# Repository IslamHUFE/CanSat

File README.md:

## CanSat

This is the repository for the project of its ambitious owner.

I hope the effort put into this will not be wasted.

### Electrical and microcontroller system

#### CanSat

#### Base station

### Mechnical

#### CanSat

#### Base station

### Documentation

### Owner

### LICENSE

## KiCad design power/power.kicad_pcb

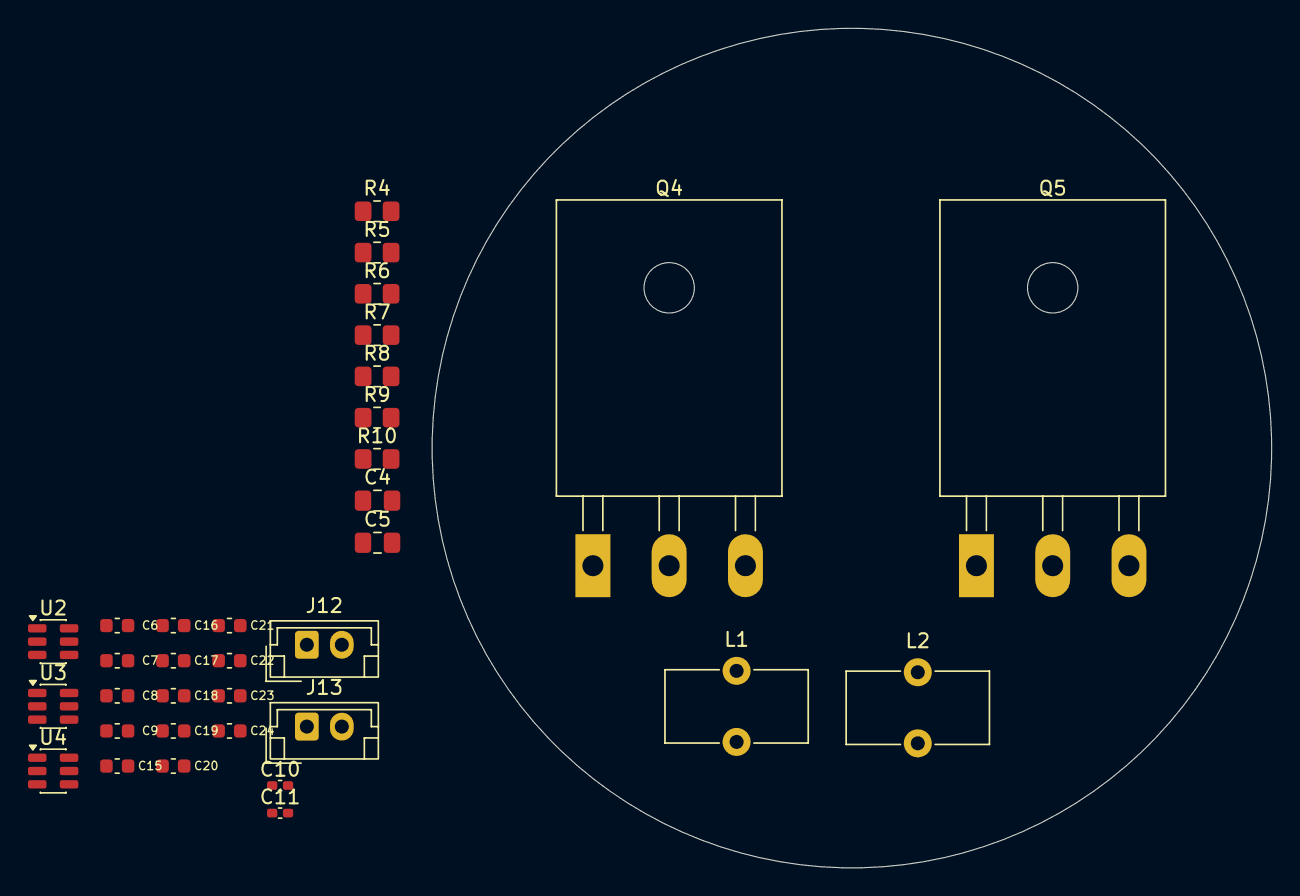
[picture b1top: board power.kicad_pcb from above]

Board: 2 copper layers, 60.0 x 60.0 mm, 34 parts (0 on the bottom side), 15 nets, no tracks yet.

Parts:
C4, C5: C_Polarized; C_0805_2012Metric_Pad1.18x1.45mm_HandSolder
C6, C7, C8, C9, C15, C16, C17, C18, C20, C21, C22, C23: 22uf/10V; C_0603_1608Metric
C10, C11: 100nf/50V; C_0402_1005Metric_Pad0.74x0.62mm_HandSolder
C19, C24: 100uf/10V; C_0603_1608Metric
J12, J13: Screw_Terminal_01x02; JST_EH_B2B-EH-A_1x02_P2.50mm_Vertical
L1, L2: 2.2uH/4.3A; L_Toroid_Vertical_L10.0mm_W5.0mm_P5.08mm
Q4, Q5: Q_NMOS; TO-247-3_Horizontal_TabDown
R4, R5, R6, R7, R8, R9, R10: R_US; R_0805_2012Metric_Pad1.20x1.40mm_HandSolder
U2: SOT-23-6
U3, U4: LM2734X; TSOT-23-6

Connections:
+3.3V: C15.2, C16.2, C17.2, C18.2, C19.2, L2.2, R9.2
+5V: C20.2, C21.2, C22.2, C23.2, C24.2, L1.2, R7.2
unnamed: C4.2, C5.2, J12.1, U2.6 (VSS)
unnamed: C5.1, J12.2, J13.1, R5.2
unnamed: R6.2, U2.3 (CS)
unnamed: R5.1, U2.4 (VC)
unnamed: R4.1, U2.5 (VDD)
unnamed: C10.1, U3.1 (BOOST)
unnamed: R7.1, R8.2, U3.3 (FB)
unnamed: C10.2, L1.1, U3.6 (SW)
unnamed: C11.1, U4.1 (BOOST)
unnamed: R9.1, R10.2, U4.3 (FB)
unnamed: C11.2, L2.1, U4.6 (SW)
PB+: C4.1, C6.1, C7.2, C8.1, C9.2, J13.2, R4.2, U3.4 (EN), U3.5 (VIN), U4.4 (EN), U4.5 (VIN)
PB-: C6.2, C7.1, C8.2, C9.1, C15.1, C16.1, C17.1, C18.1, C19.1, C20.1, C21.1, C22.1, C23.1, C24.1, R6.1, R8.1, R10.1, U3.2 (GND), U4.2 (GND)

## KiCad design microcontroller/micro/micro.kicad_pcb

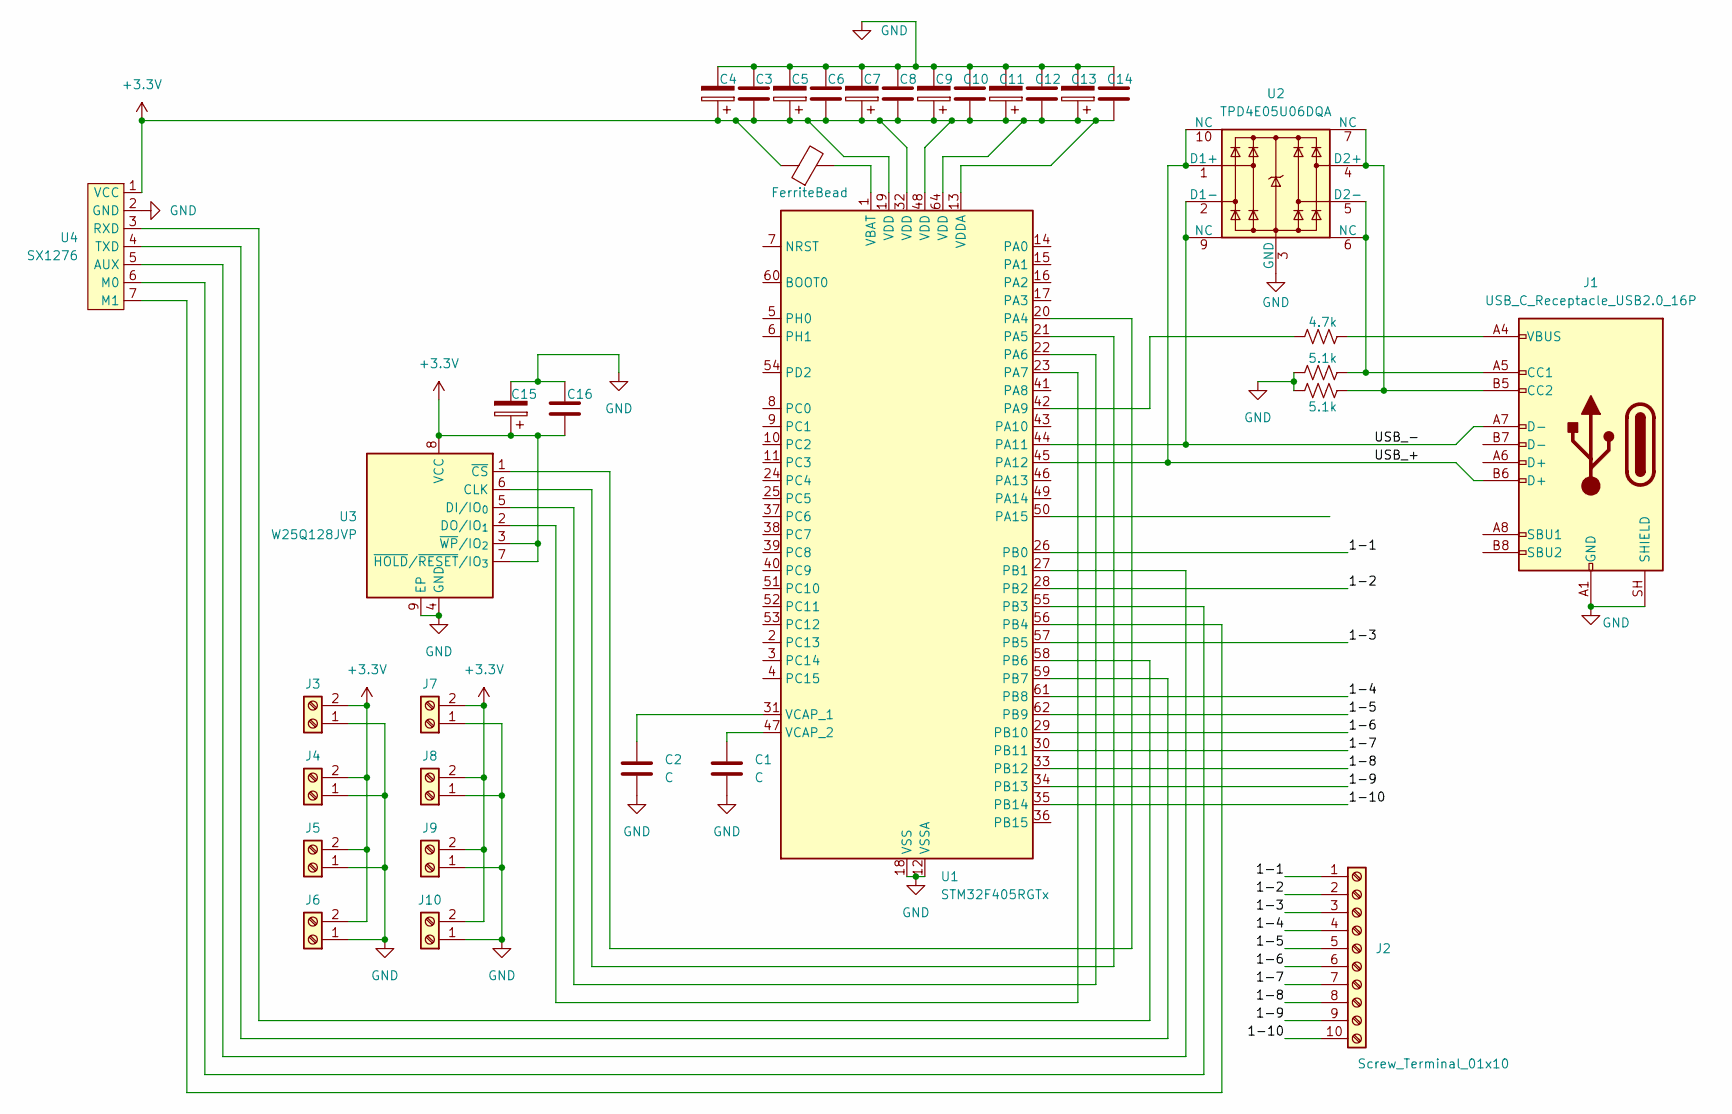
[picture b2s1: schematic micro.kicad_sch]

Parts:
C1, C2, C3, C6, C8, C10, C12, C14, C16: C; C_1206_3216Metric
C4, C5, C7, C9, C11, C13, C15: C_Polarized; CP_EIA-6032-28_Kemet-C
FB1: FerriteBead; L_Walsin_WLFM201609x
J1: USB_C_Receptacle_USB2.0_16P; USB_C_Receptacle_GCT_USB4105-xx-A_16P_TopMnt_Horizontal
J2: Screw_Terminal_01x10; PinHeader_1x10_P2.54mm_Vertical
J3, J4, J5, J6, J7, J8, J9, J10: Screw_Terminal_01x02; PinHeader_1x02_P2.54mm_Vertical
R1, R2: 5.1k; R_1206_3216Metric
R3: 4.7k; R_0603_1608Metric
U1: STM32F405RGTx; LQFP-64_10x10mm_P0.5mm
U2: TPD4E05U06DQA; USON-10_2.5x1.0mm_P0.5mm
U3: W25Q128JVP; WSON-8-1EP_6x5mm_P1.27mm_EP3.4x4.3mm
U4: SX1276; PinHeader_1x07_P2.54mm_Vertical

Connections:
+3.3V: C3.1, C4.1, C5.1, C6.1, C7.1, C8.1, C9.1, C10.1, C11.1, C12.1, C13.1, C14.1, C15.1, C16.1, FB1.1, J3.2, J4.2, J5.2, J6.2, J7.2, J8.2, J9.2, J10.2, U1.13 (VDDA), U1.19 (VDD), U1.32 (VDD), U1.48 (VDD), U1.64 (VDD), U3.3 (~WP/IO_{2}), U3.7 (~HOLD/~RESET/IO_{3}), U3.8 (VCC), U4.1 (VCC)
/1-1: J2.1, U1.26 (PB0)
/1-2: J2.2, U1.28 (PB2)
/1-3: J2.3, U1.57 (PB5)
/1-4: J2.4, U1.61 (PB8)
/1-5: J2.5, U1.62 (PB9)
/1-6: J2.6, U1.29 (PB10)
/1-7: J2.7, U1.30 (PB11)
/1-8: J2.8, U1.33 (PB12)
/1-9: J2.9, U1.34 (PB13)
/1-10: J2.10, U1.35 (PB14)
/USB_+: J1.B6 (D+), U1.45 (PA12), U2.1 (D1+), U2.10 (NC)
/USB_-: J1.A7 (D-), U1.44 (PA11), U2.2 (D1-), U2.9 (NC)
GND: C1.2, C2.2, C3.2, C4.2, C5.2, C6.2, C7.2, C8.2, C9.2, C10.2, C11.2, C12.2, C13.2, C14.2, C15.2, C16.2, J1.A1 (GND), J1.A12 (GND), J1.B1 (GND), J1.B12 (GND), J1.SH (SHIELD), J3.1, J4.1, J5.1, J6.1, J7.1, J8.1, J9.1, J10.1, R1.1, R2.1, U1.12 (VSSA), U1.18 (VSS), U1.63 (VSS), U2.3 (GND), U2.8 (GND), U3.4 (GND), U3.9 (EP), U4.2 (GND)
unnamed: J1.A5 (CC1), R2.2, U2.5 (D2-), U2.6 (NC)
unnamed: J1.B5 (CC2), R1.2, U2.4 (D2+), U2.7 (NC)
unnamed: J1.A4 (VBUS), J1.A9 (VBUS), J1.B4 (VBUS), J1.B9 (VBUS), R3.2
unnamed: U1.20 (PA4), U3.1 (~CS)
unnamed: U1.21 (PA5), U3.6 (CLK)
unnamed: U1.22 (PA6), U3.5 (DI/IO_{0})
unnamed: U1.23 (PA7), U3.2 (DO/IO_{1})
unnamed: R3.1, U1.42 (PA9)
unnamed: U1.27 (PB1), U4.5 (AUX)
unnamed: U1.55 (PB3), U4.6 (M0)
unnamed: U1.56 (PB4), U4.7 (M1)
unnamed: U1.58 (PB6), U4.3 (RXD)
unnamed: U1.59 (PB7), U4.4 (TXD)
unnamed: FB1.2, U1.1 (VBAT)
unnamed: C2.1, U1.31 (VCAP_1)
unnamed: C1.1, U1.47 (VCAP_2)

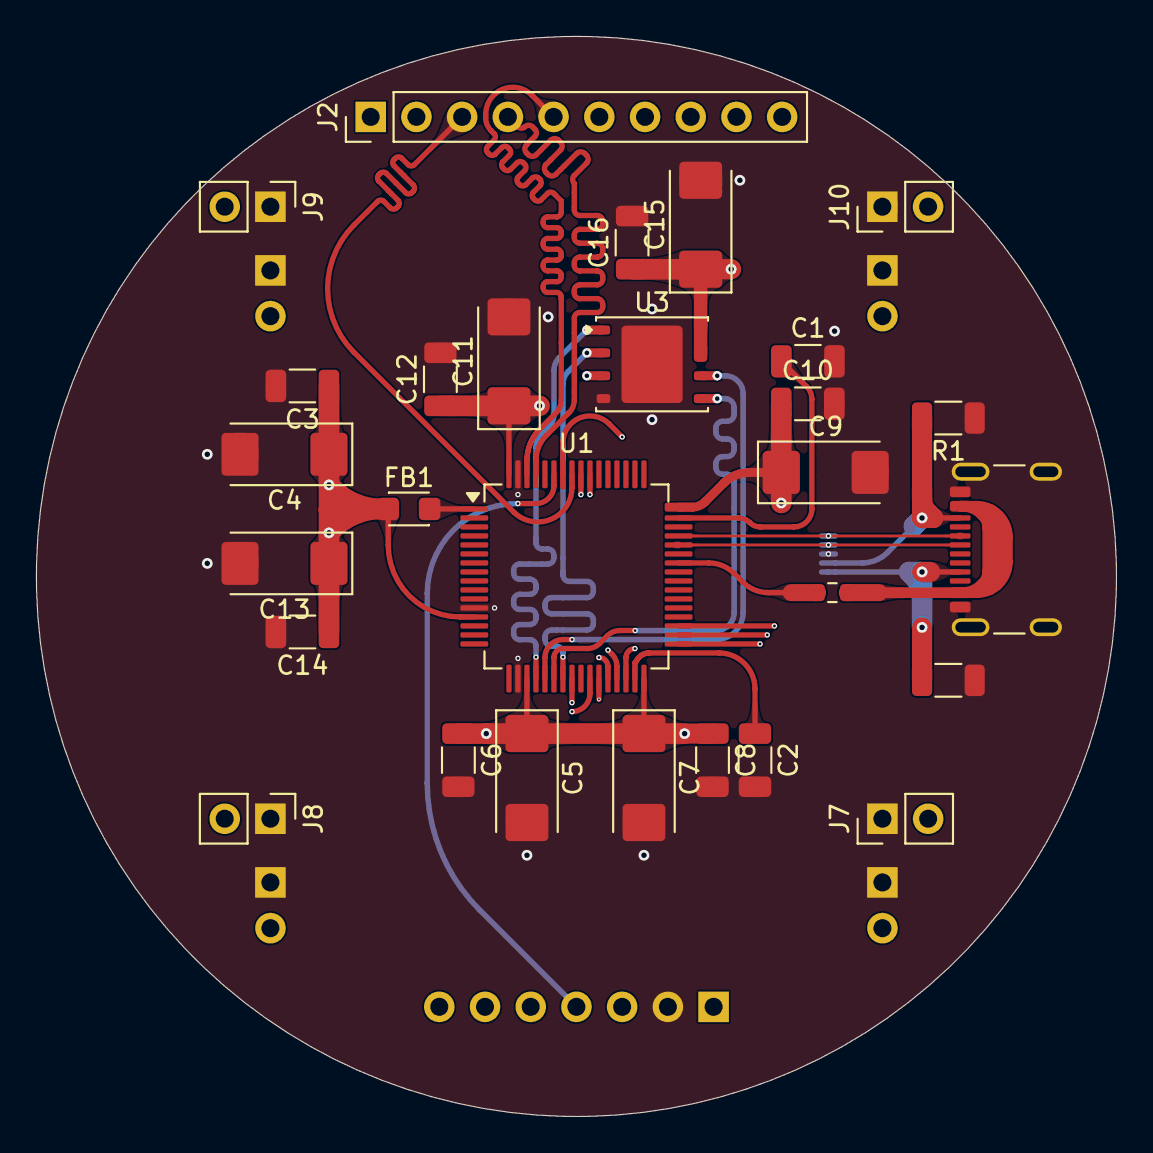
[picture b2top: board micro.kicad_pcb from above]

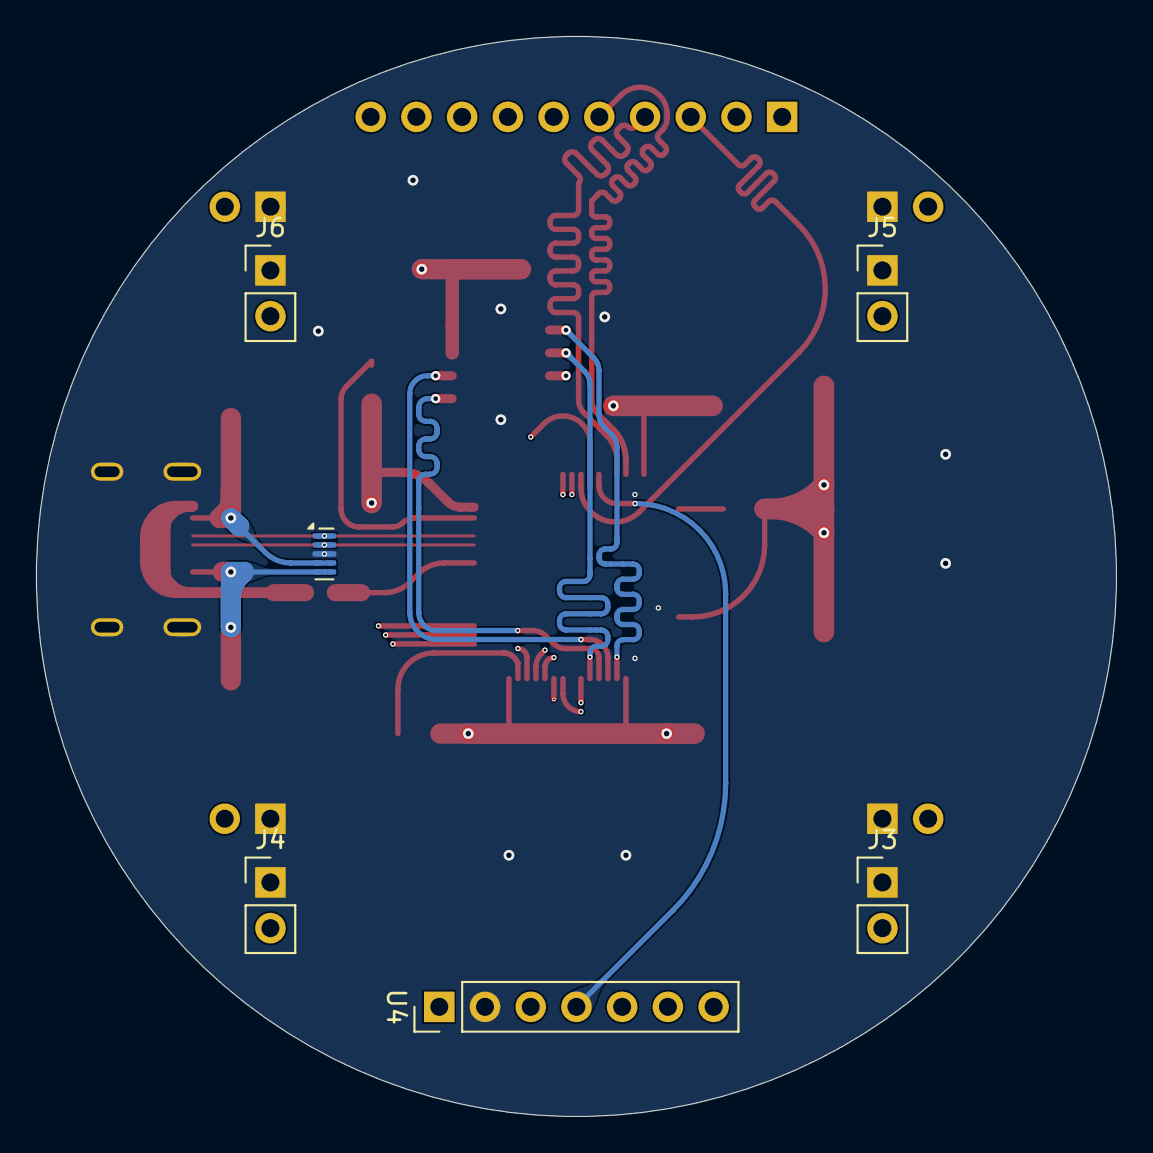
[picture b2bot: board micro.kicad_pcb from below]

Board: 6 copper layers, 60.0 x 60.0 mm, 34 parts (6 on the bottom side), 30 nets.

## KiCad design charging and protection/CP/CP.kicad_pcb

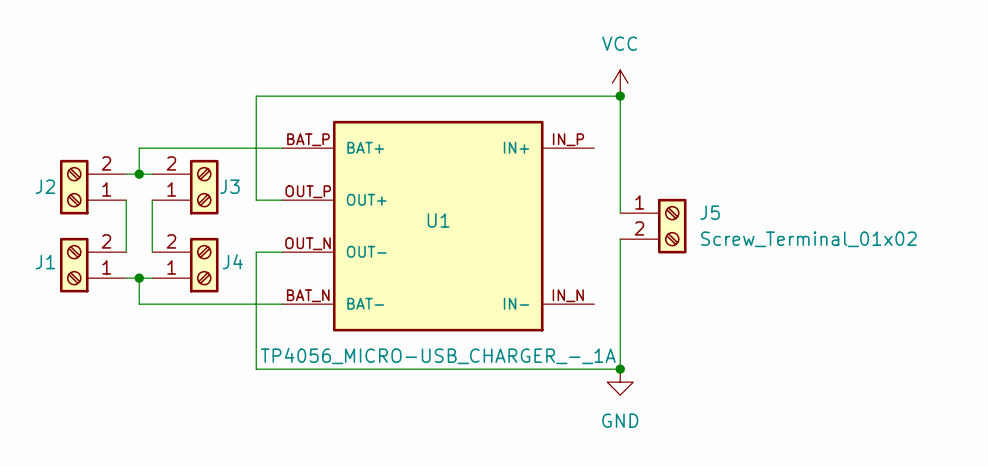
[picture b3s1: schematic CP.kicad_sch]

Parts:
J1, J2, J3, J4: Screw_Terminal_01x02; JST_EH_B2B-EH-A_1x02_P2.50mm_Vertical
J5: Screw_Terminal_01x02; AMASS_XT30PW-M_1x02_P2.50mm_Horizontal
U1: TP4056_MICRO-USB_CHARGER_-_1A; MODULE_TP4056_MICRO-USB_CHARGER_-_1A

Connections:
GND: J5.2, U1.OUT_N (OUT-)
unnamed: J1.1, J4.1, U1.BAT_N (BAT-)
unnamed: J1.2, J2.1
unnamed: J2.2, J3.2, U1.BAT_P (BAT+)
unnamed: J3.1, J4.2
VCC: J5.1, U1.OUT_P (OUT+)

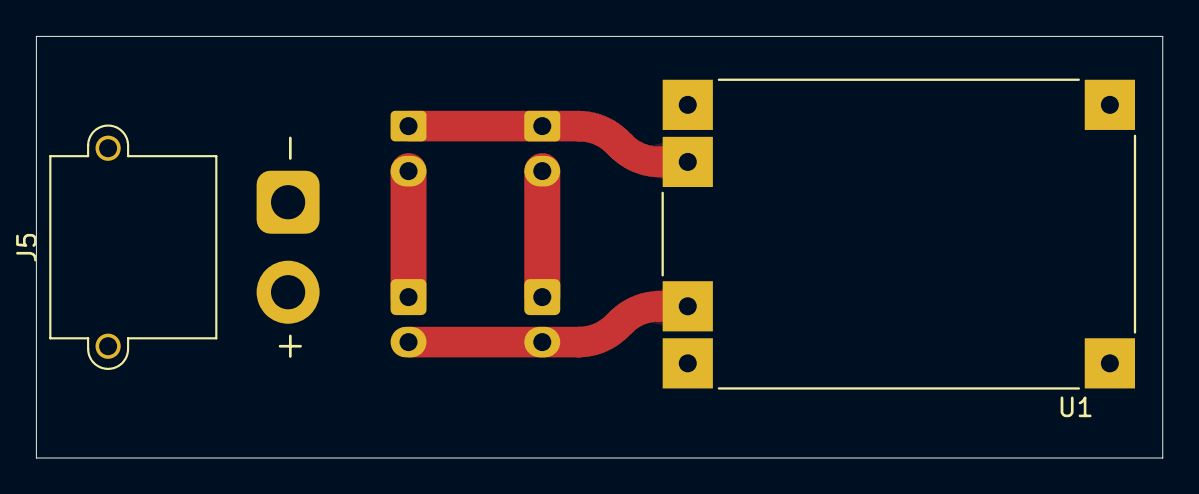
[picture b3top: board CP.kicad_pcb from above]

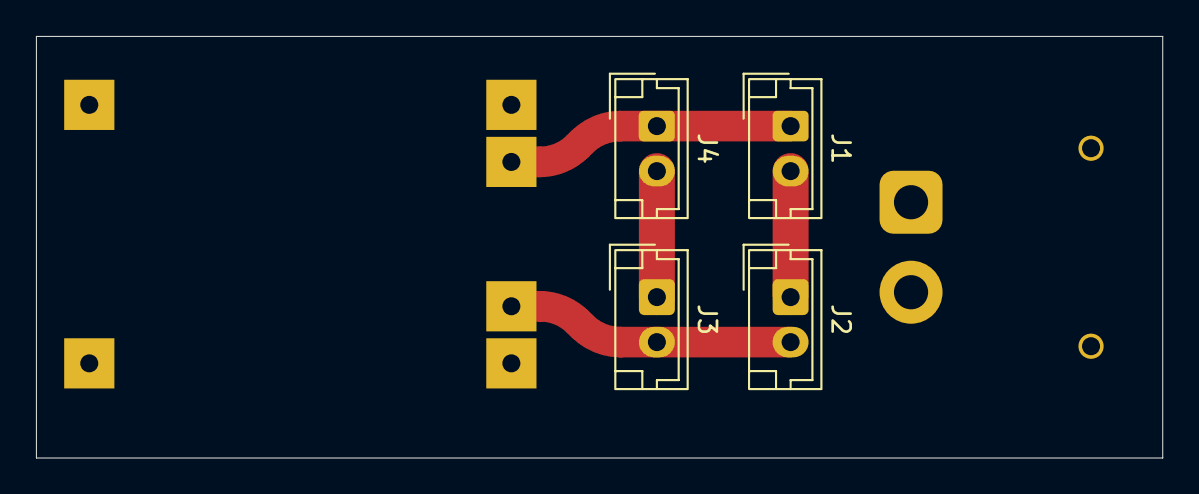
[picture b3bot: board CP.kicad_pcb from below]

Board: 2 copper layers, 62.6 x 23.4 mm, 6 parts (4 on the bottom side), 6 nets.

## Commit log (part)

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2026-05-16 Intial Commit
2026-05-16 LICENSE
2026-05-16 Update copyright and license terms in LICENSE file
2026-05-16 Update copyright holder name in LICENSE file
2026-05-16 refresh
2026-05-19 Add initial content to README.md
2026-05-19 Update README to include license section
2026-05-20 Battery charging
2026-05-27 islam
2026-06-08 length tuning
2026-06-09 Update artifact upload path in static.yml
    Change artifact upload path to specific directory.
2026-06-16 Enhance .refresh.sh with success messages
    Add feedback for successful pull and push operations.
